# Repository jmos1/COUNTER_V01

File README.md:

# COUNTER_V01

### Summary: ###
  This board is a seven-segment display stopwatch that can count up to 99 minutes.
  It uses the popular 4XXX series logic chips to drive the displays, as well as a few other popular components
  like the 555 timer to implement other functions.

  The BOM, schematic PDF, and gerber files are all accessible in the _'Outputs/'_ folder. 
  Other project files are not included because they add clutter and can be generated from the project itself in KiCad.
  Thanks.

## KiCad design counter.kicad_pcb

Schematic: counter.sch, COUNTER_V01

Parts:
7seg_milli1, 7seg_milli2, 7seg_min1, 7seg_min2, 7seg_sec1, 7seg_sec2: SC56-21GWA
C1: 1uf; CAPC2012X140N
C2: 10uf; CAPC3216X110N
C3, C5: .01uf; CAPC1608X90
C4, C6: 10uf; CAPAE430X550N
D1, D2, D3, D4: D; D_DO-41_SOD81_P7.62mm_Horizontal
D5: GRN; LED_1206_3216Metric_Castellated
J1: Barrel_Jack; BarrelJack_CUI_PJ-102AH_Horizontal
R1, R2, R3, R5, R6, R13, R14, R15, R24, R25, R33: 1K; RESC2012X70N
R4: 220; RESC1608X55N
R7, R9, R11, R18, R20, R22: 120; RESC1608X55N
R28: 10K; RESC3216X70N
S1: EG1218
SW1: Stop; SW_B3FS-1010P
SW2: Start; SW_B3FS-1010P
SW3: Reset; SW_B3FS-1010P
U1: SG531P; SOCKET_DIP-8_7.62mm_Conn
U2: 4017; CD4017BM96
U3: SN74LS74; SN74LS74ADR
U5: 4060; CD4060BM96
U6: NE555; NE555PSR
U7: LM7805MPX_NOPB; SOT-223
milli1, milli2: 4026B; CD4026BNSR
min1, min2: 4026B; CD4026BNSR
sec1, sec2: 4026B; CD4026BNSR

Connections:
100Hz: U3.9, milli1.1
200Hz: U3.11, U5.3
+5V: C1.1, C5.1, C6.1, R1.1, R4.2, R5.1, R6.1, R28.1, SW3.3, U1.8, U2.16 (VDD), U3.14, U5.16, U6.8 (VCC), U7.3, milli1.3, milli1.16, milli2.3, milli2.16, min1.3, min1.16, min2.3, min2.16, sec1.3, sec1.16, sec2.3, sec2.16
/+7-12VIN: J1.1, S1.P
GND: C2.2, C3.2, C4.2, C5.2, C6.2, D5.1 (K), J1.2, R2.2, R3.2, R7.1, R9.1, R11.1, R13.2, R14.2, R15.2, R18.1, R20.1, R22.1, R24.2, R25.2, R33.2, SW1.3, SW2.3, U1.4, U2.8 (VSS), U3.7, U5.8, U6.1 (GND), U7.2, U7.4, milli1.8, milli2.8, min1.8, min2.8, sec1.8, sec2.8
Modulo6: D1.2 (A), D4.2 (A), U2.5 (Q6), min1.1
unnamed: 7seg_milli1.1, milli1.11
unnamed: 7seg_milli1.2, milli1.9
unnamed: 7seg_milli1.4, milli1.13
unnamed: 7seg_milli1.6, milli1.12
unnamed: 7seg_milli1.7, milli1.10
unnamed: 7seg_milli1.8, R7.2
unnamed: 7seg_milli1.9, milli1.6
unnamed: 7seg_milli1.10, milli1.7
unnamed: 7seg_milli2.1, milli2.11
unnamed: 7seg_milli2.2, milli2.9
unnamed: 7seg_milli2.4, milli2.13
unnamed: 7seg_milli2.6, milli2.12
unnamed: 7seg_milli2.7, milli2.10
unnamed: 7seg_milli2.8, R18.2
unnamed: 7seg_milli2.9, milli2.6
unnamed: 7seg_milli2.10, milli2.7
unnamed: 7seg_min1.1, min1.11
unnamed: 7seg_min1.2, min1.9
unnamed: 7seg_min1.4, min1.13
unnamed: 7seg_min1.6, min1.12
unnamed: 7seg_min1.7, min1.10
unnamed: 7seg_min1.8, R11.2
unnamed: 7seg_min1.9, min1.6
unnamed: 7seg_min1.10, min1.7
unnamed: 7seg_min2.1, min2.11
unnamed: 7seg_min2.2, min2.9
unnamed: 7seg_min2.4, min2.13
unnamed: 7seg_min2.6, min2.12
unnamed: 7seg_min2.7, min2.10
unnamed: 7seg_min2.8, R22.2
unnamed: 7seg_min2.9, min2.6
unnamed: 7seg_min2.10, min2.7
unnamed: 7seg_sec1.1, sec1.11
unnamed: 7seg_sec1.2, sec1.9
unnamed: 7seg_sec1.4, sec1.13
unnamed: 7seg_sec1.6, sec1.12
unnamed: 7seg_sec1.7, sec1.10
unnamed: 7seg_sec1.8, R9.2
unnamed: 7seg_sec1.9, sec1.6
unnamed: 7seg_sec1.10, sec1.7
unnamed: 7seg_sec2.1, sec2.11
unnamed: 7seg_sec2.2, sec2.9
unnamed: 7seg_sec2.4, sec2.13
unnamed: 7seg_sec2.6, sec2.12
unnamed: 7seg_sec2.7, sec2.10
unnamed: 7seg_sec2.8, R20.2
unnamed: 7seg_sec2.9, sec2.6
unnamed: 7seg_sec2.10, sec2.7
unnamed: C3.1, U6.5 (CV)
unnamed: C4.1, S1.S, U7.1
unnamed: D1.1 (K), D2.1 (K), sec2.15
unnamed: D3.1 (K), D4.1 (K), U2.15 (Reset)
unnamed: D5.2 (A), R4.1
unnamed: R2.1, sec1.2
unnamed: R3.1, min1.2
unnamed: R5.2, U3.10
unnamed: R6.2, U3.13
unnamed: R13.1, milli2.2
unnamed: R14.1, sec2.2
unnamed: R15.1, min2.2
unnamed: R25.1, U2.13 (CKEN)
unnamed: R33.1, U5.12
unnamed: U1.5, U5.11
unnamed: U3.8, U3.12
Reset: C1.2, D2.2 (A), D3.2 (A), R24.1, SW3.1, milli1.15, milli2.15, min1.15, min2.15, sec1.15
Start: R1.2, SW2.1, U6.4 (R)
Stop: C2.1, R28.2, SW1.1, U6.2 (TR)
Strt_Stp: U6.3 (Q), milli1.2
carry_milli1: milli1.5, milli2.1
carry_milli2: milli2.5, sec1.1
carry_sec1: U2.14 (CLK), sec1.5, sec2.1
min1_carry: min1.5, min2.1

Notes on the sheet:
Start, Stop & Reset
Power
3.2768 Mhz CLK & Frequency Divider
Sixty-Second Reset
7-Segment Displays & Drivers

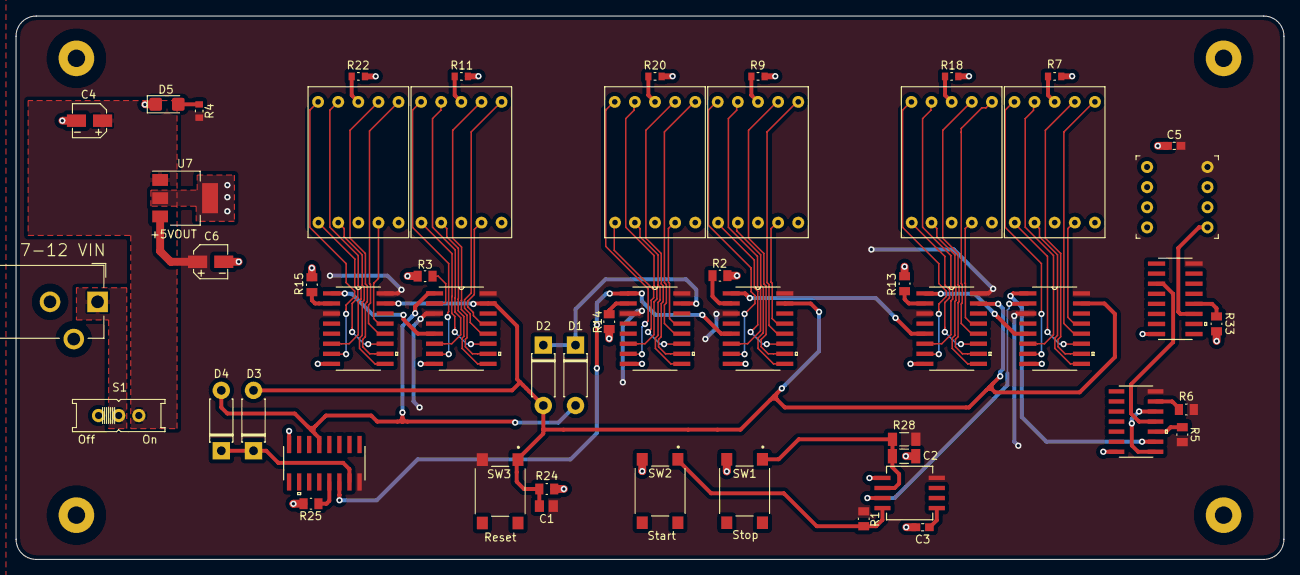
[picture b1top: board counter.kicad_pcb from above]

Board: 2 copper layers, 160.0 x 68.6 mm, 57 parts (0 on the bottom side), 78 nets.

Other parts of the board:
m2, m2#2, m2#3, m2#4: MountingHole_2.2mm_M2_ISO7380_Pad

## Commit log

2020-03-07 First commit just to save. Board is still incomplete.
2020-03-07 Cleaned up schematic and pcb. Created annotations.
2020-03-09 Changed layout, organized traces, removed resistors from 7-seg displays
2020-03-17 added gerbers, footprints, schematic pdf, symbols, 3d models
2020-03-26 Reorganized project and added missing carry_sec1 trace
2020-03-26 Create blah
2020-04-09 Rev 2 board. Added missing trace, gerbers, and schematic
2020-04-09 Schematic PDF addded
2020-06-16 Modifications to Schematic
2020-06-16 Adding BOM

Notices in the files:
parts and their libraries:
Copyright 2016 Accelerated Designs. All rights reserved.
